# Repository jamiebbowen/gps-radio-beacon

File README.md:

# GPS Radio Beacon

A long-range rocket-tracking system: an airborne **transmitter** continuously
reports GPS position over LoRa, and a handheld **receiver** displays bearing,
distance, and altitude to help recover the rocket after landing.

Tested on a Mach-0.99 / 2 km AGL flight with a 37 dB link margin — see
[`docs/flight-analysis.md`](docs/flight-analysis.md) for post-flight tooling.

## System overview

```
+-------------------------+           LoRa 433 MHz          +-------------------------+
|       TRANSMITTER       |  - - - - - - - - - - - - - ->  |         RECEIVER        |
|  (flies with the rocket)|   ~15+ km LoS (SF10/62.5kHz)  |   (handheld ground)     |
+-------------------------+                                 +-------------------------+
  - ItsyBitsy M4 (SAMD51)                                     - STM32F401 Black Pill
  - u-blox GPS (UART)                                         - NEO-6M GPS (UART)
  - BNO085 IMU (I2C) - launch detect                          - BNO085 IMU (I2C) - compass
  - E22-400M33S LoRa (SPI)                                    - E22 LoRa (SPI)
  - Power: 3.3 V + LiPo                                       - SSD1309 OLED (I2C)
                                                              - microSD log (SPI, littlefs)
```

The transmitter runs a state machine (`TURN_ON` -> `PRE_LAUNCH` -> `LAUNCH` ->
`POST_LAUNCH` -> `BATTERY_SAVE`) that auto-adapts TX cadence based on IMU-detected liftoff.
The receiver logs every packet to SD card for post-flight analysis.

## Repository layout

```
.
|-- transmitter/
|   |-- firmware/            Arduino/C++ code for the ItsyBitsy M4
|   |                        (radio, GPS, IMU, beacon state machine)
|   `-- pcb/                 KiCad schematic + PCB design
|
|-- receiver/
|   |-- firmware/            Bare-metal STM32 HAL code
|   |                        (radio, GPS, compass, OLED, SD card, navigation UI)
|   `-- tools/
|       `-- analyze_flight.py  Post-flight log analyzer + KML/MP4 renderer
|
|-- tools/
|   |-- log_summary.py       Field-log health forensics (wedges, watchdogs,
|   |                          telemetry gaps) - run on a session directory
|   `-- lfs_extract/         Pull Lxxxxxxx.TXT logs off the littlefs SD image
|
|-- docs/                    Reference documentation (wiring, radio config,
|                            reliability, troubleshooting)
|   `-- archive/             Historical bug post-mortems and migration notes
|
`-- README.md                This file
```

## Quick start

### Transmitter (ItsyBitsy M4)

```bash
cd transmitter/firmware
make install-deps     # one-time: installs arduino-cli + Adafruit SAMD core
make compile ID=3 CHANNEL=5   # per-airframe rocket ID and channel
make flash ID=3 CHANNEL=5     # flashes via /dev/ttyACM0 by default
make monitor          # optional: USB serial log
```

Edit `include/mpu_config.h` to set your amateur-radio callsign.

### Receiver (STM32F401)

```bash
cd receiver/firmware
make                  # builds bin/gps_radio_beacon_receiver.elf
make flash            # explicit flash step
```

### Flight analysis

After a flight, pull the SD card from the receiver and extract the logs
(the card is littlefs, not FAT):

```bash
make extract DEV=/dev/sdX                        # -> flight_data/<timestamp>/
python3 tools/log_summary.py flight_data/<ts>/   # health audit in seconds
python3 receiver/tools/analyze_flight.py flight_data/<ts>/L0001.TXT
```

Options:

| Flag | Purpose |
|---|---|
| `--kml flight.kml` | Google-Earth replay with time-animated rocket track |
| `--mp4 flight.mp4` | Headless 3-D animated replay (matplotlib + ffmpeg) |
| `--duration 15` | Compress flight into N-second video |
| `--sensitivity -134` | Override receiver sensitivity for range prediction |

Prints altitude, velocity, slant range, RSSI/SNR trace, predicted max range,
and packet-continuity statistics. See
[`docs/flight-analysis.md`](docs/flight-analysis.md) for details.

## Documentation

Detailed reference docs live in [`docs/`](docs/):

- **Hardware wiring**: receiver and transmitter pin assignments
- **LoRa radio**: E22-400M33S configuration and link-budget notes
- **Launch detection**: BNO085 IMU threshold tuning
- **GPS watchdog**: automatic recovery from fix loss
- **Reliability**: signal-quality monitoring, staleness, validation
- **SD card troubleshooting**: diagnostics for the receiver logger
- **Flight analysis**: using `analyze_flight.py`

Post-mortems of specific bug fixes are preserved under
[`docs/archive/`](docs/archive/).

## License / legal

The LoRa link operates on the 433 MHz band. In the US this falls under the
amateur-radio 70 cm allocation; the beacon transmits its callsign every
few minutes for FCC compliance. **Check your local regulations and hold
an appropriate license before transmitting.**

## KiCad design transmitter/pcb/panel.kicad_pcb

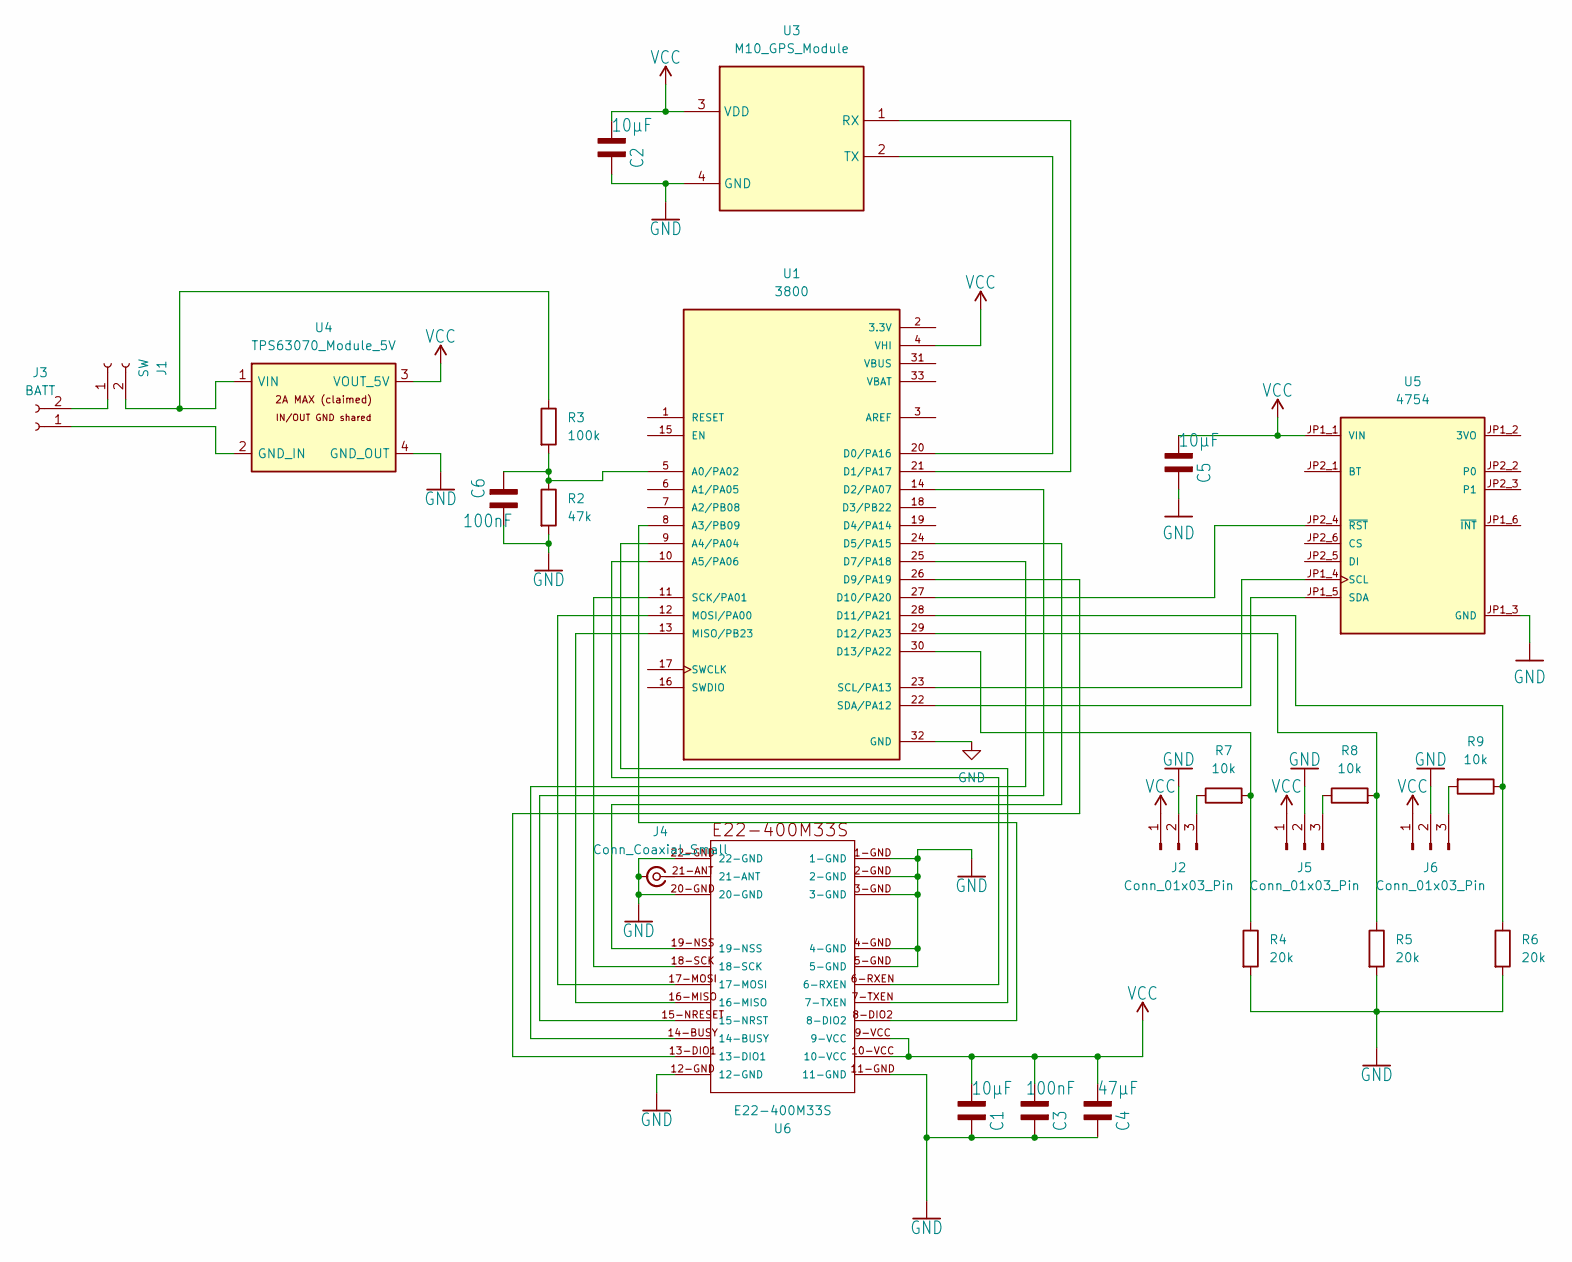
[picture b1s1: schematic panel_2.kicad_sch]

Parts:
C1, C2, C5: 10µF; C_0805_2012Metric_Pad1.18x1.45mm_HandSolder
C3, C6: 100nF; C_0805_2012Metric_Pad1.18x1.45mm_HandSolder
C4: 47µF; C_0805_2012Metric_Pad1.18x1.45mm_HandSolder
J1: SW; JST_PH_B2B-PH-K_1x02_P2.00mm_Vertical
J2, J5, J6: Conn_01x03_Pin; PinHeader_1x03_P2.54mm_Vertical
J3: BATT; JST_PH_B2B-PH-K_1x02_P2.00mm_Vertical
J4: Conn_Coaxial_Small; SMA_Amphenol_901-143_Horizontal
R2: 47k; R_0603_1608Metric
R3: 100k; R_0603_1608Metric
R4, R5, R6: 20k; R_0603_1608Metric
R7, R8, R9: 10k; R_0603_1608Metric
U1: 3800; MODULE_3800; PARTREV B
U3: M10_GPS_Module; M10 GPS Module
U4: TPS63070_Module_5V; Teyleten_TPS63070_5V_Module_THT
U5: 4754; MODULE_4754; PARTREV 2021-03-16
U6: E22-400M33S

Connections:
GND: C1.2, C2.2, C3.2, C4.2, C5.2, C6.1, J2.2, J4.2 (Ext), J5.2, J6.2, R2.2, R4.2, R5.2, R6.2, U1.32 (GND), U3.4 (GND), U4.4 (GND_OUT), U5.JP1_3 (GND), U6.1-GND, U6.2-GND, U6.3-GND, U6.4-GND, U6.5-GND, U6.11-GND, U6.12-GND, U6.20-GND, U6.22-GND
unnamed: J1.1, J3.2
unnamed: J1.2, R3.1, U4.1 (VIN)
unnamed: J2.3, R7.1
unnamed: J3.1, U4.2 (GND_IN)
unnamed: J4.1 (In), U6.21-ANT
unnamed: J5.3, R8.1
unnamed: J6.3, R9.2
unnamed: C6.2, R2.1, R3.2, U1.5 (A0/PA02)
unnamed: U1.8 (A3/PB09), U6.8-DIO2
unnamed: U1.9 (A4/PA04), U6.7-TXEN
unnamed: U1.10 (A5/PA06), U6.6-RXEN
unnamed: U1.20 (D0/PA16), U3.2 (TX)
unnamed: U1.21 (D1/PA17), U3.1 (RX)
unnamed: U1.14 (D2/PA07), U6.15-NRESET (15-NRST)
unnamed: U1.24 (D5/PA15), U6.19-NSS
unnamed: U1.25 (D7/PA18), U6.14-BUSY
unnamed: U1.26 (D9/PA19), U6.13-DIO1
unnamed: U1.27 (D10/PA20), U5.JP2_4 (~RST)
unnamed: R6.1, R9.1, U1.28 (D11/PA21)
unnamed: R5.1, R8.2, U1.29 (D12/PA23)
unnamed: R4.1, R7.2, U1.30 (D13/PA22)
unnamed: U1.13 (MISO/PB23), U6.16-MISO
unnamed: U1.12 (MOSI/PA00), U6.17-MOSI
unnamed: U1.11 (SCK/PA01), U6.18-SCK
unnamed: U1.23 (SCL/PA13), U5.JP1_4 (SCL)
unnamed: U1.22 (SDA/PA12), U5.JP1_5 (SDA)
VCC: C1.1, C2.1, C3.1, C4.1, C5.1, J2.1, J5.1, J6.1, U1.4 (VHI), U3.3 (VDD), U4.3 (VOUT_5V), U5.JP1_1 (VIN), U6.9-VCC, U6.10-VCC

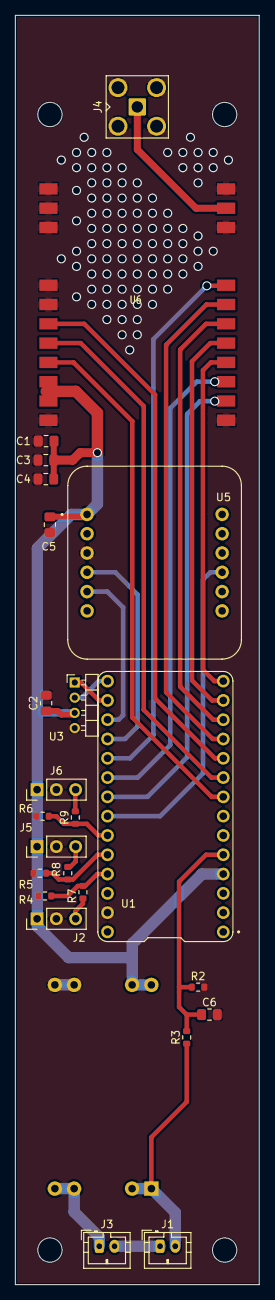
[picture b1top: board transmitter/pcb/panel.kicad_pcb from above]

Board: 2 copper layers, 32.1 x 167.1 mm, 29 parts (1 on the bottom side), 28 nets.

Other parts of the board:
MH1, MH2, MH3, MH4: MountingHole_3.2mm_M3

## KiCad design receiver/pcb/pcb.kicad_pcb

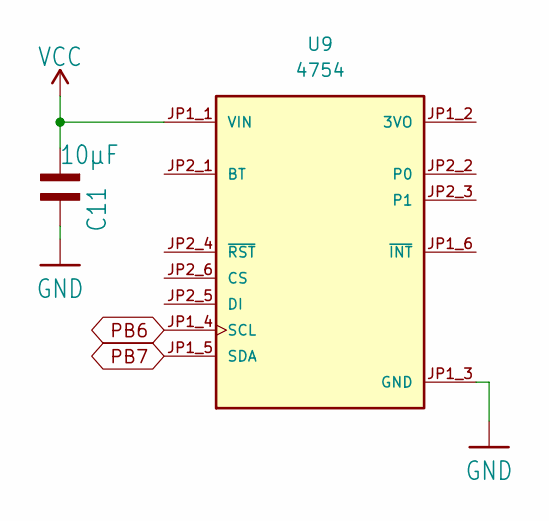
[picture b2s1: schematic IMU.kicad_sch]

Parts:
C11: 10µF; C_0805_2012Metric_Pad1.18x1.45mm_HandSolder
U9: 4754; MODULE_4754; PARTREV 2021-03-16

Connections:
FP_GND: C11.2, U9.JP1_3 (GND); also elsewhere on the board
FP_PB6: U9.JP1_4 (SCL); also elsewhere on the board
FP_PB7: U9.JP1_5 (SDA); also elsewhere on the board
FP_VCC: C11.1, U9.JP1_1 (VIN); also elsewhere on the board

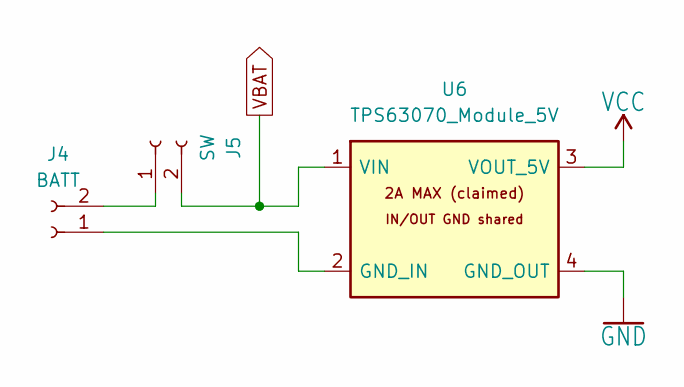
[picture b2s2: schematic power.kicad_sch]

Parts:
J4: BATT; JST_PH_B2B-PH-K_1x02_P2.00mm_Vertical
J5: SW; JST_PH_B2B-PH-K_1x02_P2.00mm_Vertical
U6: TPS63070_Module_5V; Teyleten_TPS63070_5V_Module_THT

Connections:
FP_GND: U6.4 (GND_OUT); also elsewhere on the board
FP_VCC: U6.3 (VOUT_5V); also elsewhere on the board
unnamed: J4.1, U6.2 (GND_IN)
unnamed: J4.2, J5.1
VBAT: J5.2, U6.1 (VIN); also elsewhere on the board

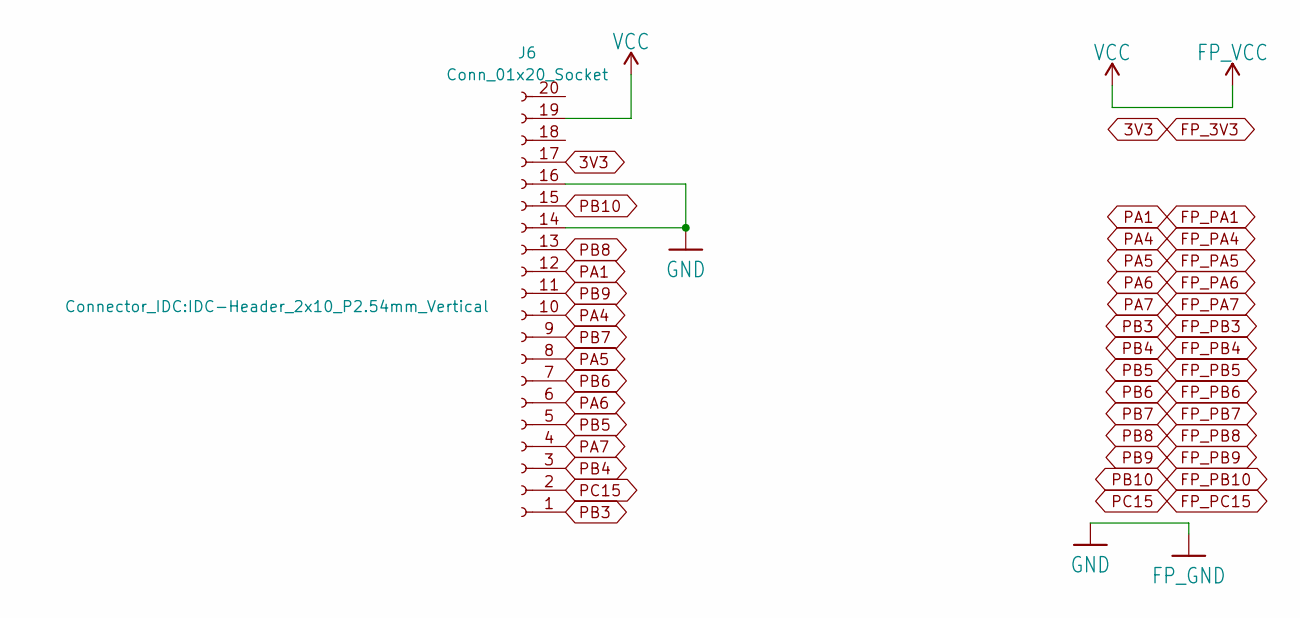
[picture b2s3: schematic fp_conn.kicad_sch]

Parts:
J6: Conn_01x20_Socket; IDC-Header_2x10_P2.54mm_Vertical

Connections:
3V3: J6.17; also elsewhere on the board
FP_GND: J6.14, J6.16; also elsewhere on the board
FP_PA1: J6.12; also elsewhere on the board
FP_PA4: J6.10; also elsewhere on the board
FP_PA5: J6.8; also elsewhere on the board
FP_PA6: J6.6; also elsewhere on the board
FP_PA7: J6.4; also elsewhere on the board
FP_PB3: J6.1; also elsewhere on the board
FP_PB4: J6.3; also elsewhere on the board
FP_PB5: J6.5; also elsewhere on the board
FP_PB6: J6.7; also elsewhere on the board
FP_PB7: J6.9; also elsewhere on the board
FP_PB8: J6.13; also elsewhere on the board
FP_PB9: J6.11; also elsewhere on the board
FP_PB10: J6.15; also elsewhere on the board
FP_PC15: J6.2; also elsewhere on the board
FP_VCC: J6.19; also elsewhere on the board

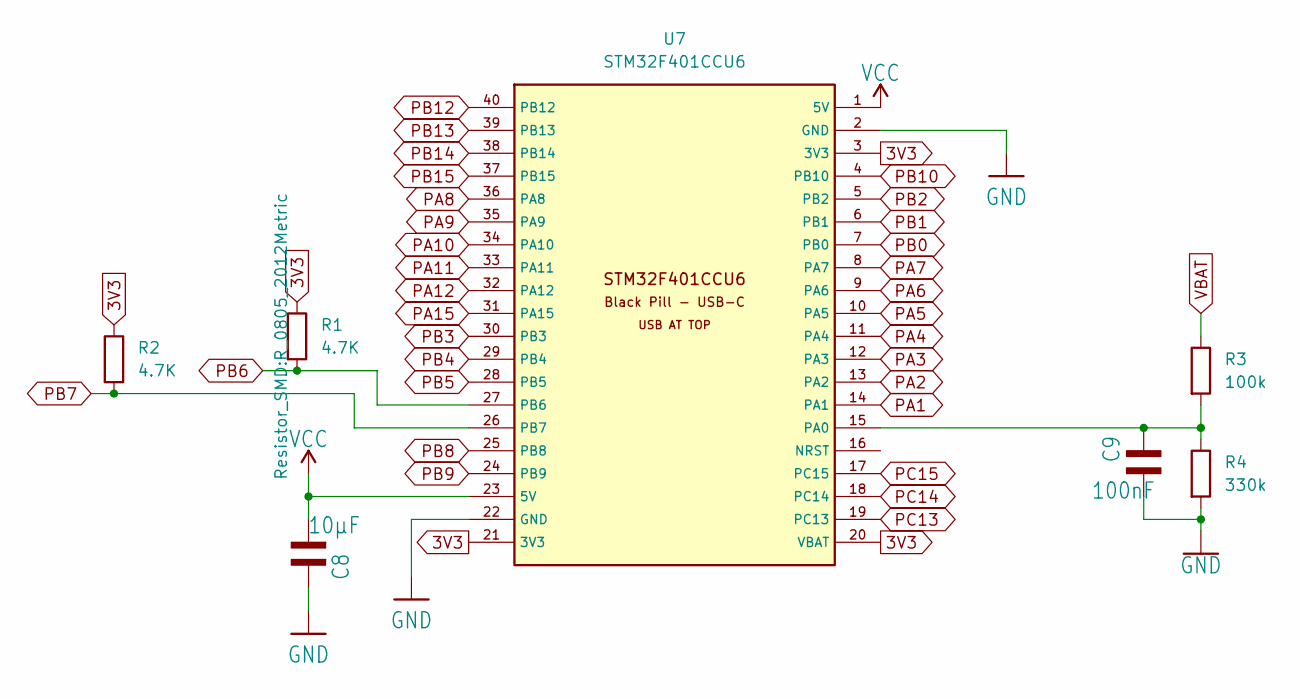
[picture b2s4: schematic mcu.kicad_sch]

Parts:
C8: 10µF; C_0805_2012Metric_Pad1.18x1.45mm_HandSolder
C9: 100nF; C_0805_2012Metric_Pad1.18x1.45mm_HandSolder
R1, R2: 4.7K; R_0805_2012Metric
R3: 100k; R_0603_1608Metric
R4: 330k; R_0603_1608Metric
U7: STM32F401CCU6; STM32F401CCU6_BlackPill_2x20; PARTREV B

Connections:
3V3: R1.1, R2.1, U7.3 (3V3), U7.20 (VBAT), U7.21 (3V3); also elsewhere on the board
FP_GND: C8.2, C9.1, R4.2, U7.2 (GND), U7.22 (GND); also elsewhere on the board
FP_PA1: U7.14 (PA1); also elsewhere on the board
FP_PA4: U7.11 (PA4); also elsewhere on the board
FP_PA5: U7.10 (PA5); also elsewhere on the board
FP_PA6: U7.9 (PA6); also elsewhere on the board
FP_PA7: U7.8 (PA7); also elsewhere on the board
FP_PB3: U7.30 (PB3); also elsewhere on the board
FP_PB4: U7.29 (PB4); also elsewhere on the board
FP_PB5: U7.28 (PB5); also elsewhere on the board
FP_PB6: R1.2, U7.27 (PB6); also elsewhere on the board
FP_PB7: R2.2, U7.26 (PB7); also elsewhere on the board
FP_PB8: U7.25 (PB8); also elsewhere on the board
FP_PB9: U7.24 (PB9); also elsewhere on the board
FP_PB10: U7.4 (PB10); also elsewhere on the board
FP_PC15: U7.17 (PC15); also elsewhere on the board
FP_VCC: C8.1, U7.1 (5V), U7.23 (5V); also elsewhere on the board
unnamed: C9.2, R3.2, R4.1, U7.15 (PA0)
PA2: U7.13 (PA2); also elsewhere on the board
PA3: U7.12 (PA3); also elsewhere on the board
PA8: U7.36 (PA8); also elsewhere on the board
PA9: U7.35 (PA9); also elsewhere on the board
PA10: U7.34 (PA10); also elsewhere on the board
PA11: U7.33 (PA11); also elsewhere on the board
PA12: U7.32 (PA12); also elsewhere on the board
PA15: U7.31 (PA15); also elsewhere on the board
PB0: U7.7 (PB0)
PB1: U7.6 (PB1)
PB2: U7.5 (PB2)
PB12: U7.40 (PB12); also elsewhere on the board
PB13: U7.39 (PB13); also elsewhere on the board
PB14: U7.38 (PB14); also elsewhere on the board
PB15: U7.37 (PB15); also elsewhere on the board
PC13: U7.19 (PC13)
PC14: U7.18 (PC14)
VBAT: R3.1; also elsewhere on the board

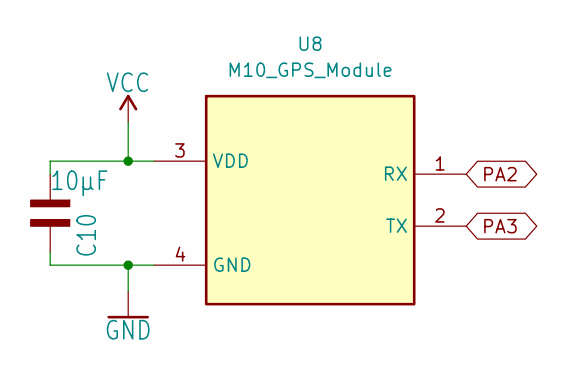
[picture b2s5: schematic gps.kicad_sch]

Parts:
C10: 10µF; C_0805_2012Metric_Pad1.18x1.45mm_HandSolder
U8: M10_GPS_Module; M10 GPS Module

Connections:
FP_GND: C10.2, U8.4 (GND); also elsewhere on the board
FP_VCC: C10.1, U8.3 (VDD); also elsewhere on the board
PA2: U8.1 (RX); also elsewhere on the board
PA3: U8.2 (TX); also elsewhere on the board

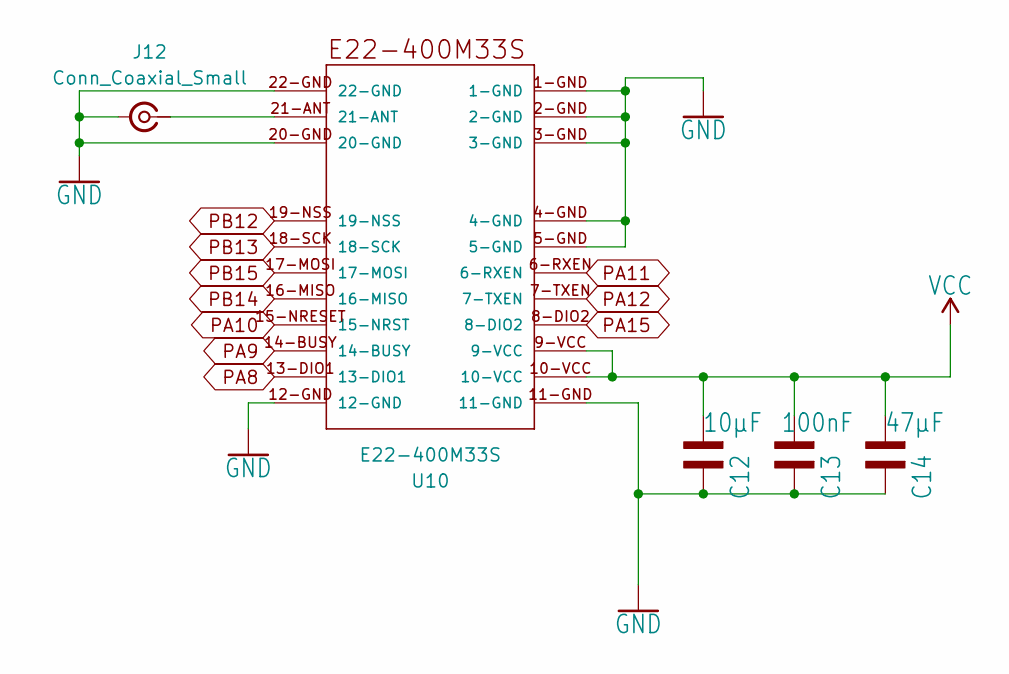
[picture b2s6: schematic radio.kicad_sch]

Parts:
C12: 10µF; C_0805_2012Metric_Pad1.18x1.45mm_HandSolder
C13: 100nF; C_0805_2012Metric_Pad1.18x1.45mm_HandSolder
C14: 47µF; C_0805_2012Metric_Pad1.18x1.45mm_HandSolder
J12: Conn_Coaxial_Small; SMA_Amphenol_901-143_Horizontal
U10: E22-400M33S

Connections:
FP_GND: C12.2, C13.2, C14.2, J12.2 (Ext), U10.1-GND, U10.2-GND, U10.3-GND, U10.4-GND, U10.5-GND, U10.11-GND, U10.12-GND, U10.20-GND, U10.22-GND; also elsewhere on the board
FP_VCC: C12.1, C13.1, C14.1, U10.9-VCC, U10.10-VCC; also elsewhere on the board
unnamed: J12.1 (In), U10.21-ANT
PA8: U10.13-DIO1; also elsewhere on the board
PA9: U10.14-BUSY; also elsewhere on the board
PA10: U10.15-NRESET (15-NRST); also elsewhere on the board
PA11: U10.6-RXEN; also elsewhere on the board
PA12: U10.7-TXEN; also elsewhere on the board
PA15: U10.8-DIO2; also elsewhere on the board
PB12: U10.19-NSS; also elsewhere on the board
PB13: U10.18-SCK; also elsewhere on the board
PB14: U10.16-MISO; also elsewhere on the board
PB15: U10.17-MOSI; also elsewhere on the board

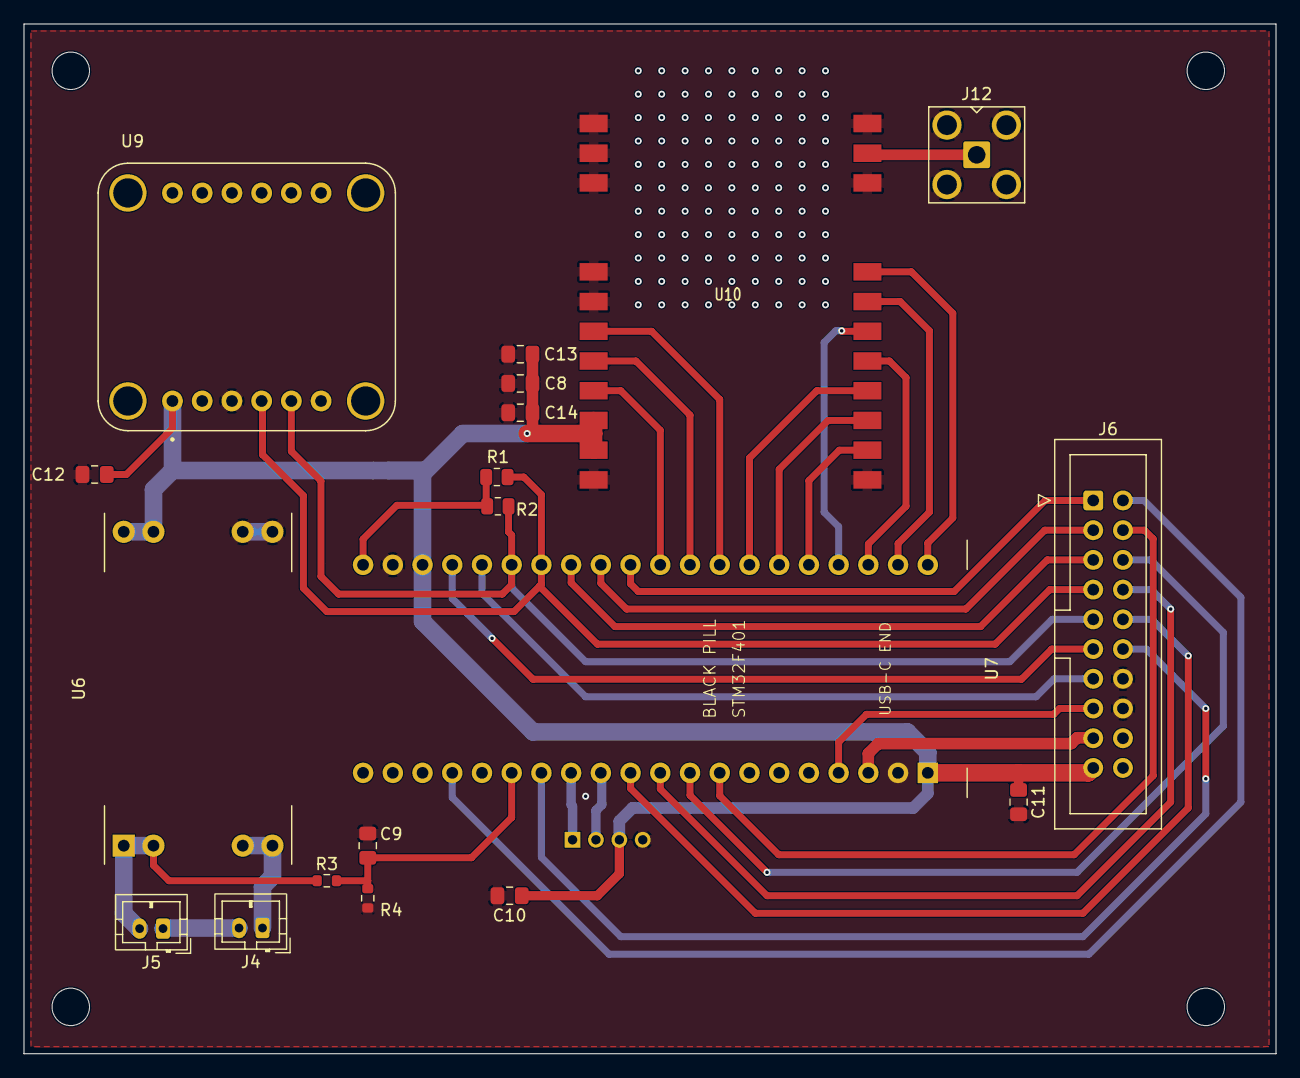
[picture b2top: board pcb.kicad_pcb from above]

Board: 2 copper layers, 107.0 x 88.0 mm, 24 parts (1 on the bottom side), 34 nets.

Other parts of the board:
MH1, MH2, MH3, MH4: MountingHole_3.2mm_M3

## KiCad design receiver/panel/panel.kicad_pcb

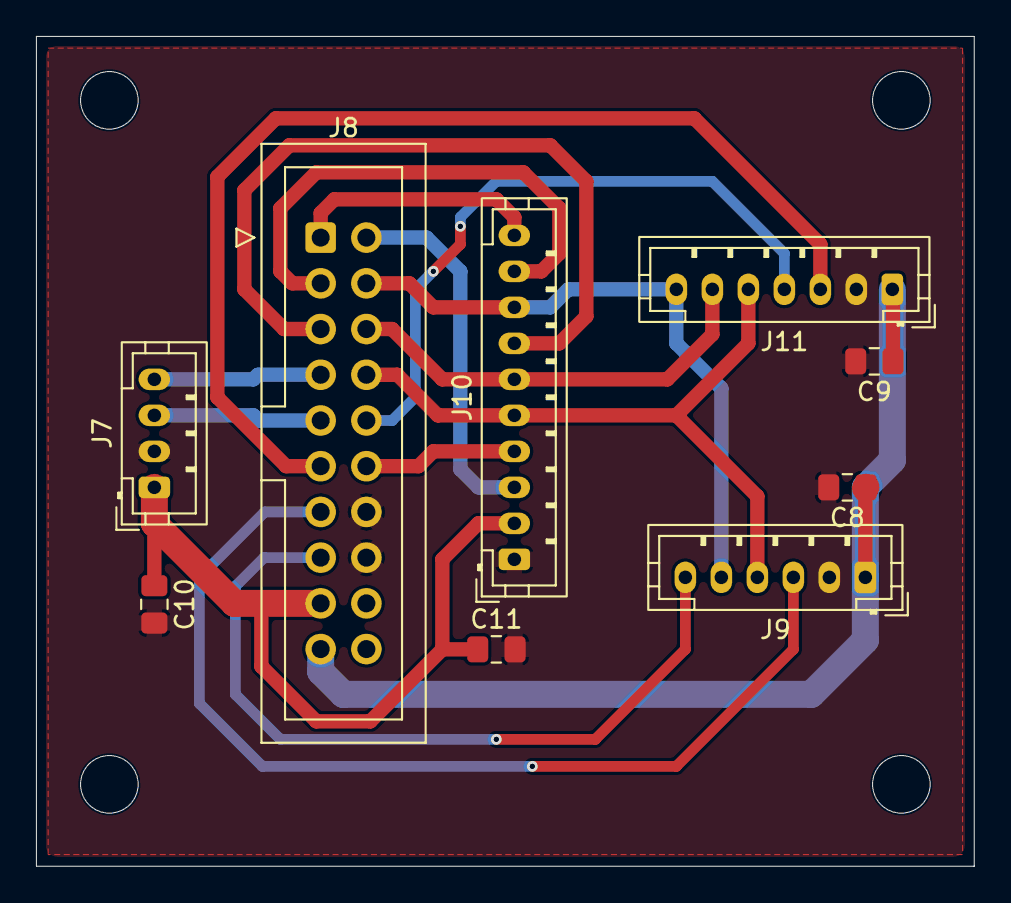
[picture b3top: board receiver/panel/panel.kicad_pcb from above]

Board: 2 copper layers, 52.1 x 46.1 mm, 13 parts (0 on the bottom side), 17 nets.

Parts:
C8, C9, C10, C11: 10µF; C_0805_2012Metric_Pad1.18x1.45mm_HandSolder
J7: Conn_01x04_Socket; JST_PH_B4B-PH-K_1x04_P2.00mm_Vertical
J8: Conn_01x20_Socket; IDC-Header_2x10_P2.54mm_Vertical
J9: Conn_01x06_Socket; JST_PH_B6B-PH-K_1x06_P2.00mm_Vertical
J10: Conn_01x10_Socket; JST_PH_B10B-PH-K_1x10_P2.00mm_Vertical
J11: Conn_01x07_Socket; JST_PH_B7B-PH-K_1x07_P2.00mm_Vertical
MH1, MH2, MH3, MH4: MountingHole_3.2mm_M3

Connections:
FP_3V3: C10.1, C11.1, J7.1, J8.17, J10.2
FP_GND: C8.2, C9.2, C10.2, C11.2, J7.2, J8.14, J8.16, J9.2, J10.1, J11.2
FP_PA1: J8.12, J10.4
FP_PA4: J8.10, J11.4
FP_PA5: J8.8, J9.4, J10.5, J11.5
FP_PA6: J8.6, J10.6, J11.6
FP_PA7: J8.4, J9.5, J10.8, J11.7
FP_PB3: J8.1, J10.10
FP_PB4: J8.3, J10.9
FP_PB5: J8.5, J10.7
FP_PB6: J7.4, J8.7
FP_PB7: J7.3, J8.9
FP_PB8: J8.13, J9.3
FP_PB9: J8.11, J11.3
FP_PB10: J8.15, J9.6
FP_PC15: J8.2, J10.3
FP_VCC: C8.1, C9.1, J8.19, J9.1, J11.1

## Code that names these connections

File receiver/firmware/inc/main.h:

/**
 * @file main.h
 * @brief Main header file for the GPS Radio Beacon Receiver
 */

#ifndef __MAIN_H
#define __MAIN_H

#ifdef __cplusplus
extern "C" {
#endif

/* Includes ------------------------------------------------------------------*/
#include "stm32f4xx_hal.h"

/* Private includes ----------------------------------------------------------*/
/* USER CODE BEGIN Includes */
#include "gps.h"
#include "compass.h"
/* USER CODE END Includes */

/* Exported types ------------------------------------------------------------*/
/* Exported constants --------------------------------------------------------*/
/* Exported macro ------------------------------------------------------------*/
/* Exported functions prototypes ---------------------------------------------*/
/* USER CODE BEGIN EFP */
void SystemClock_Config(void);
void MX_GPIO_Init(void);
void MX_SPI1_Init(void);

/* (Display mode prototypes live in inc/display_modes/<page>.h - a second
 *  copy here drifted out of date once and broke the build.) */
/* USER CODE END EFP */
void Error_Handler(void);

/* Private defines -----------------------------------------------------------*/
#define LED_PIN                     GPIO_PIN_13
#define LED_GPIO_PORT               GPIOC

/* SD Card SPI Configuration */
#define SD_SPI_INSTANCE             SPI1
#define SD_CS_PIN                   GPIO_PIN_4
#define SD_CS_GPIO_PORT             GPIOA
#define SD_DETECT_PIN               GPIO_PIN_9
#define SD_DETECT_GPIO_PORT         GPIOB  /* Moved from PA8 to PB9 to avoid LoRa RESET conflict */

/* SPI1 Pin Configuration */
#define SD_SPI_SCK_PIN              GPIO_PIN_5
#define SD_SPI_SCK_GPIO_PORT        GPIOA
#define SD_SPI_MISO_PIN             GPIO_PIN_6
#define SD_SPI_MISO_GPIO_PORT       GPIOA
#define SD_SPI_MOSI_PIN             GPIO_PIN_7
#define SD_SPI_MOSI_GPIO_PORT       GPIOA

/* --------------------------------------------------------------------------
 * Receiver v2.0 hardware (see docs/hardware-receiver.md v2.0)
 * SPI1 is a shared bus: SD card + SHARP memory LCD + SSD1680 eInk (+ SRAM).
 * NOTE mixed CS polarity: SHARP CS is ACTIVE HIGH, everything else LOW.
 * ------------------------------------------------------------------------- */

/* SHARP Memory LCD (Adafruit 3502, 168x144) on SPI1 */
#define SHARP_CS_PIN                GPIO_PIN_10  /* PB10 - CS, ACTIVE HIGH */
#define SHARP_CS_GPIO_PORT          GPIOB
#define SHARP_DISP_PIN              GPIO_PIN_8   /* PB8 - display on/off */
#define SHARP_DISP_GPIO_PORT        GPIOB

/* SSD1680 2.9" tri-color eInk FeatherWing (Adafruit 4778) on SPI1 */
#define EINK_CS_PIN                 GPIO_PIN_15  /* PC15 - ECS, active low (was PB11, which
                                                    the BlackPill 2x20 header doesn't expose;
                                                    PC15 is free - no RTC/LSE in this build) */
#define EINK_CS_GPIO_PORT           GPIOC
#define EINK_DC_PIN                 GPIO_PIN_3   /* PB3 - Data/Command */
#define EINK_DC_GPIO_PORT           GPIOB
#define EINK_RST_PIN                GPIO_PIN_4   /* PB4 - eInk reset */
#define EINK_RST_GPIO_PORT          GPIOB
#define EINK_BUSY_PIN               GPIO_PIN_1   /* PA1 - busy, HIGH = busy */
#define EINK_BUSY_GPIO_PORT         GPIOA
#define EINK_SRCS_PIN               GPIO_PIN_5   /* PB5 - SRAM CS (wired, unused:
                                                    framebuffer lives in MCU RAM) */
#define EINK_SRCS_GPIO_PORT         GPIOB

/* Battery voltage divider: 100k over 330k, midpoint -> PA0 (ADC1_IN0).
 * Full-scale 4.30V -> 3.3V; 100nF to GND at the midpoint steadies the
 * ~77k source resistance (requires 480-cycle sampling). */
#define BATTERY_ADC_PIN             GPIO_PIN_0
#define BATTERY_ADC_GPIO_PORT       GPIOA
#define BATTERY_ADC_CHANNEL         ADC_CHANNEL_0

#ifdef __cplusplus
}
#endif

#endif /* __MAIN_H */

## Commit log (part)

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2026-04-19 Initial commit: import existing firmware, docs, and tools
    - Transmitter firmware (ItsyBitsy M4 / Arduino)
    - Receiver firmware (STM32F401 / bare-metal HAL)
    - Flight-analysis tool (receiver/tools/analyze_flight.py)
    - Scattered design/reliability/troubleshooting docs at root
    - KiCad PCB files for transmitter
    - Expanded .gitignore to cover firmware build artifacts, KiCad
2026-04-19 Reorganize docs into docs/ and docs/archive/
    Consolidate 14 scattered root-level MD files plus 8 scattered firmware
    docs into a structured docs/ directory:
    docs/
    README.md index of all docs
    hardware-receiver.md (from RECEIVER_WIRING.md)
    hardware-transmitter.md (from TRANSMITTER_PINOUTS.md)
